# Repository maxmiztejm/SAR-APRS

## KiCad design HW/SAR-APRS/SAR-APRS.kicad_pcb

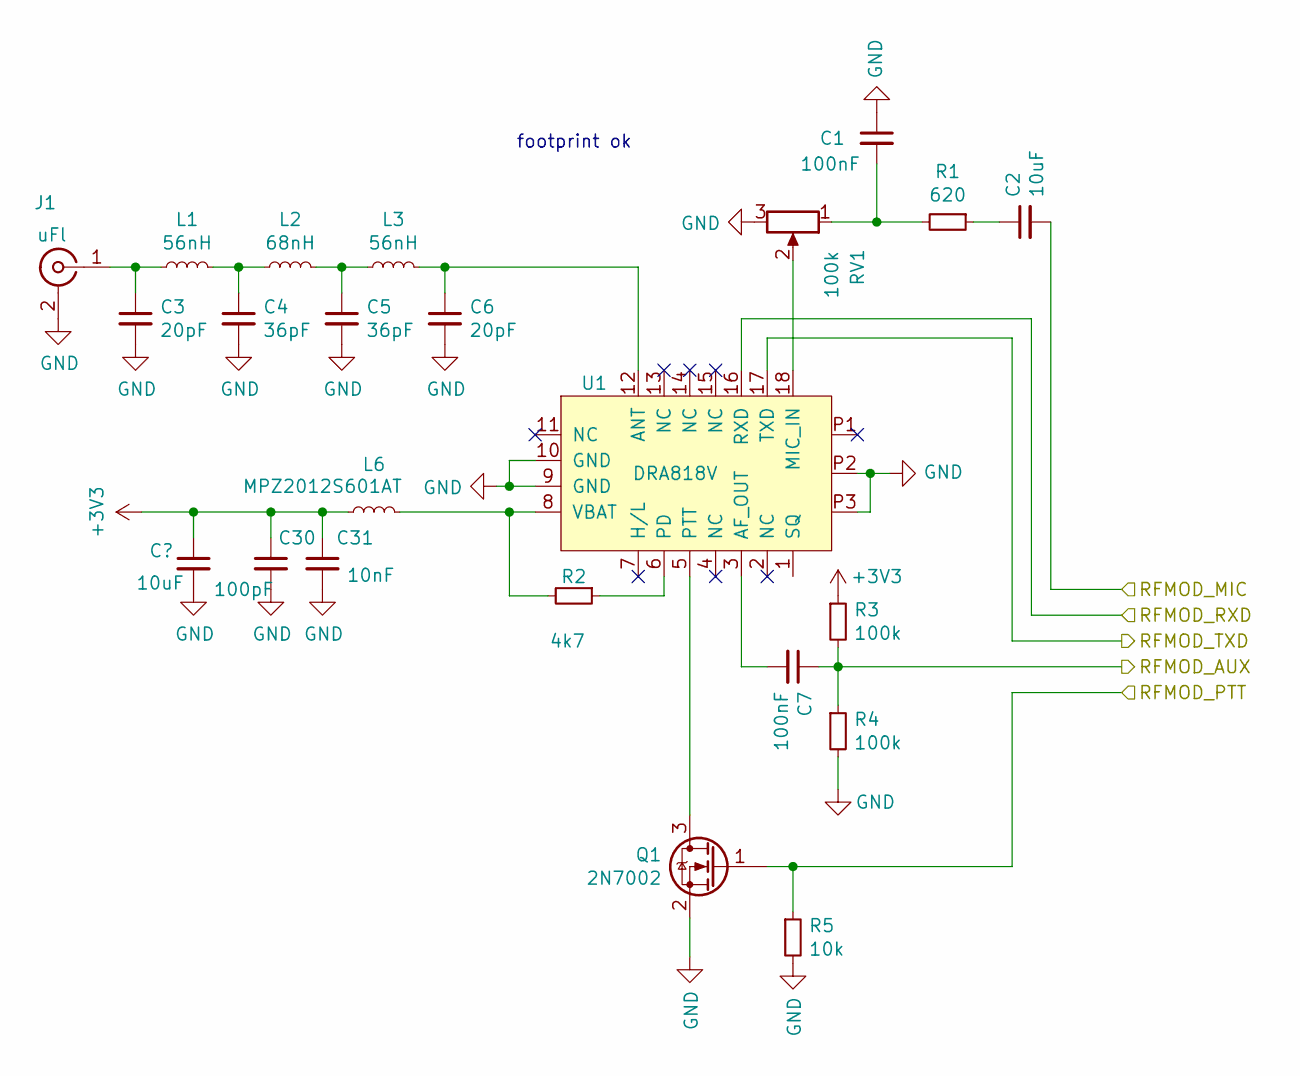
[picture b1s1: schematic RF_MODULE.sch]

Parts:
C1, C7: 100nF; C_0805
C2: 10uF; C_0805
C3, C6: 20pF; C_0805
C4, C5: 36pF; C_0805
C30: 100pF; C_0603
C31: 10nF; C_0603
J1: uFl; sma_straight_32k101-400l5
L1, L3: 56nH; L_0805
L2: 68nH; L_0805
L6: MPZ2012S601AT; C_0805
Q1: 2N7002; SOT-23
R1: 620; R_0805
R2: 4k7; R_0805
R3, R4: 100k; R_0805
R5: 10k; R_0805
RV1: 100k; Potentiometer_Trimmer_Bourns_3214J
U1: DRA818V; DRA818

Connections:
/CPU/RFMOD_AUX: C7.1, R3.2, R4.1; also elsewhere on the board
/CPU/RFMOD_MIC: C2.2; also elsewhere on the board
/CPU/RFMOD_PTT: Q1.1 (G), R5.1; also elsewhere on the board
/CPU/RFMOD_RXD: U1.16 (RXD); also elsewhere on the board
/CPU/RFMOD_TXD: U1.17 (TXD); also elsewhere on the board
GND: C1.1, C3.2, C4.2, C5.2, C6.2, C30.2, C31.2, J1.2 (Ext), Q1.2 (S), R4.2, R5.2, RV1.3, U1.9 (GND), U1.10 (GND), U1.P2, U1.P3; also elsewhere on the board
unnamed: C1.2, R1.2, RV1.1
unnamed: C2.1, R1.1
unnamed: C3.1, J1.1 (In), L1.1
unnamed: C4.1, L1.2, L2.1
unnamed: C5.1, L2.2, L3.1
unnamed: C6.1, L3.2, U1.12 (ANT)
unnamed: C7.2, U1.3 (AF_OUT)
unnamed: L6.2, R2.2, U1.8 (VBAT)
unnamed: Q1.3 (D), U1.5 (PTT)
unnamed: R2.1, U1.6 (PD)
unnamed: RV1.2, U1.18 (MIC_IN)

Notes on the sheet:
footprint ok

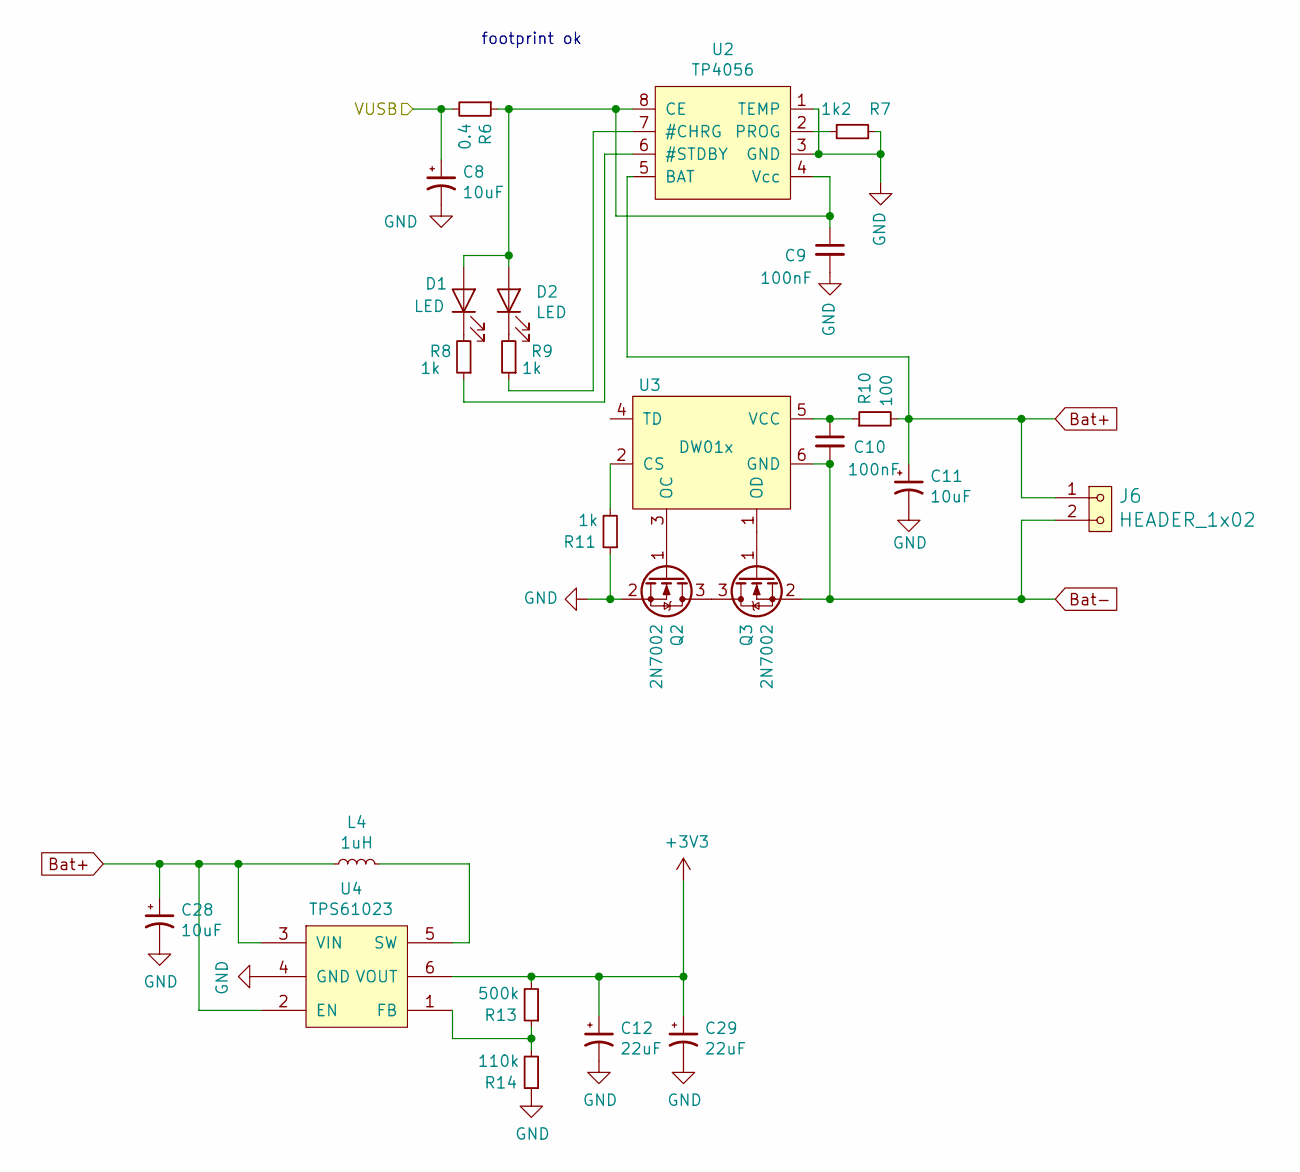
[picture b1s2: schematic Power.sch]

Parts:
C8, C11, C28: 10uF; C_1210
C9, C10: 100nF; C_0805
C12, C29: 22uF; C_1210
D1, D2: LED; LED_0805
J6: HEADER_1x02; Straight_1x02
L4: 1uH; L_6.3x6.3_H3
Q2, Q3: 2N7002; SOT-23
R6: 0.4; R_2512
R7: 1k2; R_0805
R8, R9, R11: 1k; R_0805
R10: 100; R_0805
R13: 500k; R_0805
R14: 110k; R_0805
U2: TP4056; SO-8_3.9x4.9mm_P1.27mm
U3: DW01x; SOT-23-6
U4: TPS61023; SOT-563

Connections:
/CPU/VUSB: C8.1, R6.2; also elsewhere on the board
Bat+: C11.1, C28.1, J6.1, L4.1, R10.2, U2.5 (BAT), U4.2 (EN), U4.3 (VIN); also elsewhere on the board
Bat-: C10.2, J6.2, Q3.2 (S), U3.6 (GND)
GND: C8.2, C9.2, C11.2, C12.2, C28.2, C29.2, Q2.2 (S), R7.2, R11.1, R14.1, U2.1 (TEMP), U2.3 (GND), U4.4 (GND); also elsewhere on the board
unnamed: C9.1, D1.2 (A), D2.2 (A), R6.1, U2.4 (Vcc), U2.8 (CE)
unnamed: C10.1, R10.1, U3.5 (VCC)
unnamed: D1.1 (K), R8.2
unnamed: D2.1 (K), R9.2
unnamed: L4.2, U4.5 (SW)
unnamed: Q2.1 (G), U3.3 (OC)
unnamed: Q2.3 (D), Q3.3 (D)
unnamed: Q3.1 (G), U3.1 (OD)
unnamed: R7.1, U2.2 (PROG)
unnamed: R8.1, U2.6 (#STDBY)
unnamed: R9.1, U2.7 (#CHRG)
unnamed: R11.2, U3.2 (CS)
unnamed: R13.1, R14.2, U4.1 (FB)

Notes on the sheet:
footprint ok

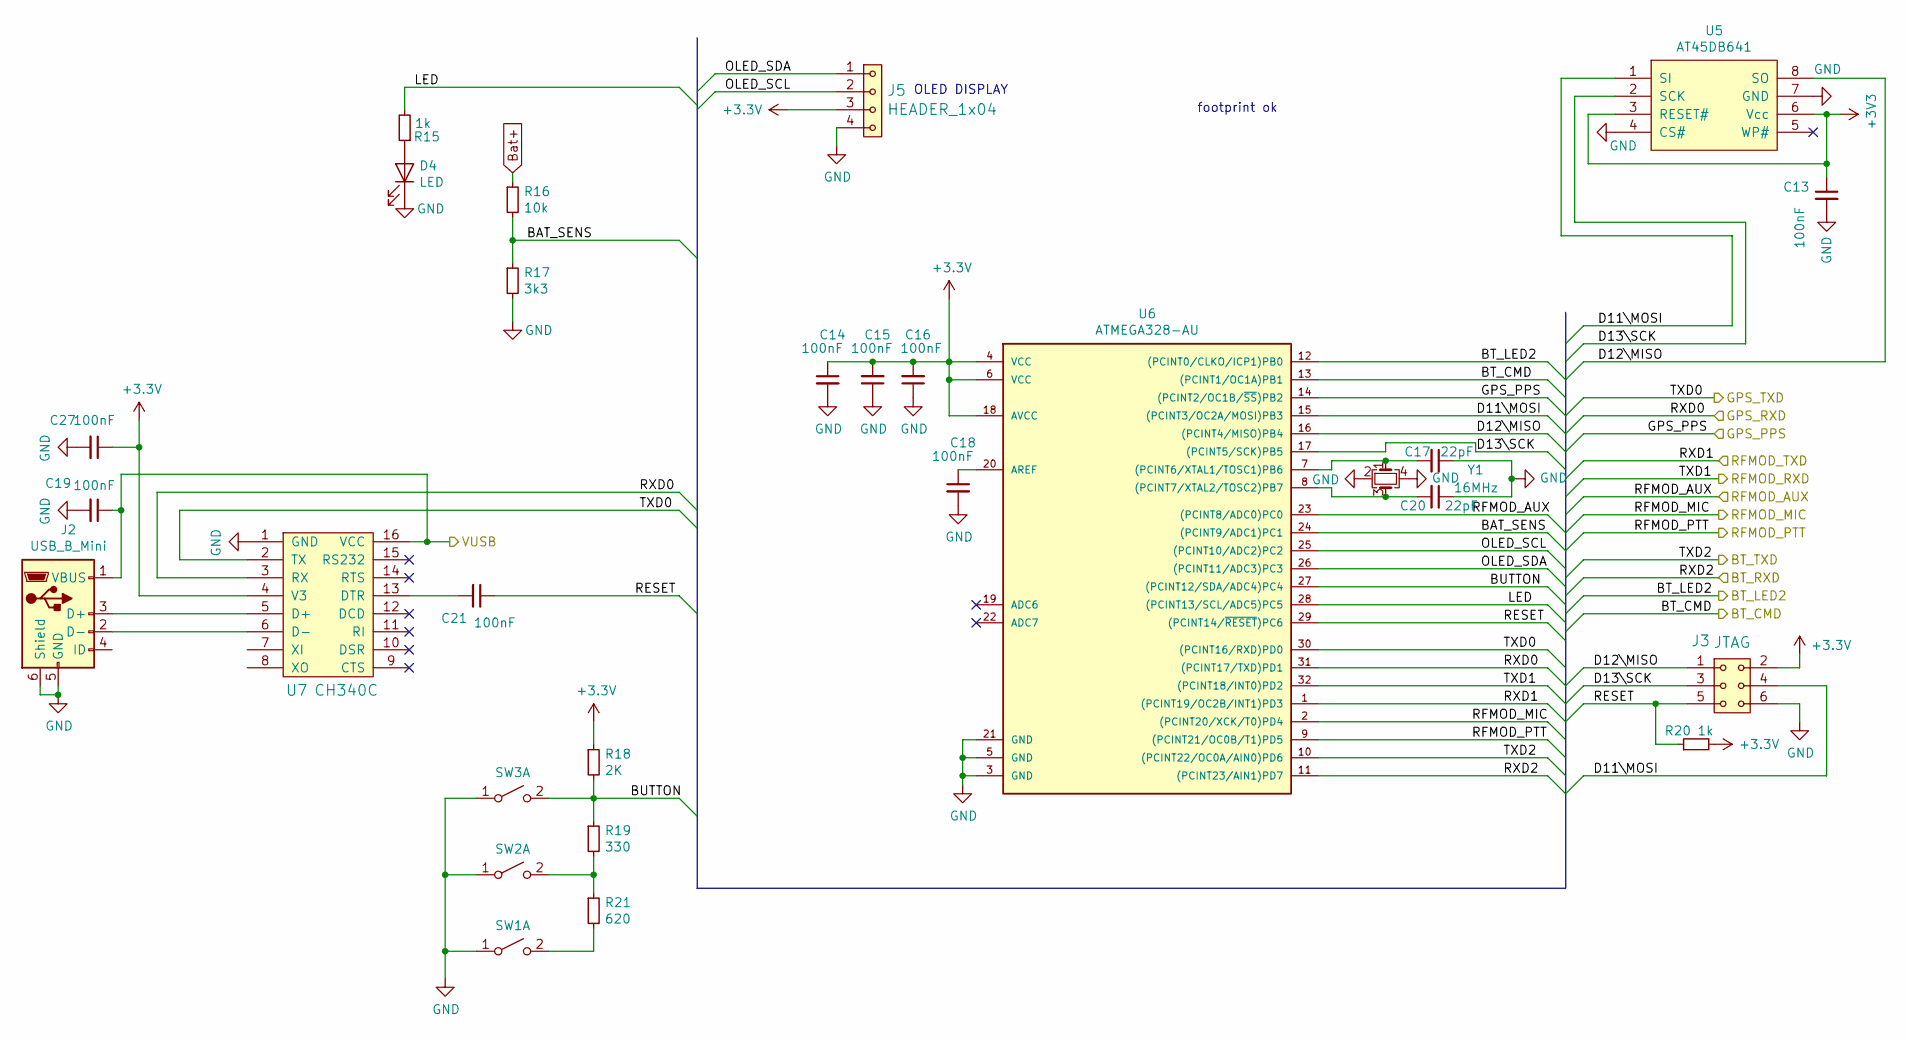
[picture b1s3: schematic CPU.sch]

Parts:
C13, C14, C15, C16, C18, C19, C21, C27: 100nF; C_0805
C17, C20: 22pF; C_0805
D4: LED; LED_0805
J2: USB_B_Mini; USB_Mini-B
J3: JTAG; Straight_2x03
J5: HEADER_1x04; Straight_1x04
R15, R20: 1k; R_0805
R16: 10k; R_0805
R17: 3k3; R_0805
R18: 2K; R_0805
R19: 330; R_0805
R21: 620; R_0805
SW1, SW2, SW3: SW_DPST_x2; SW_SPST_EVQP0
U5: AT45DB641; SOIC-8_3.9x4.9mm_Pitch1.27mm
U6: ATMEGA328-AU; TQFP-32_7x7mm_Pitch0.8mm
U7: CH340C; SOP-16_4.55x10.3mm_P1.27mm
Y1: 16MHz; ISM81

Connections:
/BT_module/BT_CMD: U6.13 ((PCINT1/OC1A)PB1); also elsewhere on the board
/BT_module/BT_LED2: U6.12 ((PCINT0/CLKO/ICP1)PB0); also elsewhere on the board
/BT_module/BT_RXD: U6.11 ((PCINT23/AIN1)PD7); also elsewhere on the board
/BT_module/BT_TXD: U6.10 ((PCINT22/OC0A/AIN0)PD6); also elsewhere on the board
/CPU/BAT_SENS: R16.2, R17.1, U6.24 ((PCINT9/ADC1)PC1)
/CPU/BUTTON: R18.2, R19.1, SW3.2 (B), U6.27 ((PCINT12/SDA/ADC4)PC4)
/CPU/D11\MOSI: J3.4, U5.1 (SI), U6.15 ((PCINT3/OC2A/MOSI)PB3)
/CPU/D12\MISO: J3.1, U5.8 (SO), U6.16 ((PCINT4/MISO)PB4)
/CPU/D13\SCK: J3.3, U5.2 (SCK), U6.17 ((PCINT5/SCK)PB5)
/CPU/GPS_PPS: U6.14 ((PCINT2/OC1B/~SS~)PB2); also elsewhere on the board
/CPU/GPS_RXD: U6.31 ((PCINT17/TXD)PD1), U7.3 (RX); also elsewhere on the board
/CPU/LED: R15.2, U6.28 ((PCINT13/SCL/ADC5)PC5)
/CPU/OLED_SCL: J5.2, U6.25 ((PCINT10/ADC2)PC2)
/CPU/OLED_SDA: J5.1, U6.26 ((PCINT11/ADC3)PC3)
/CPU/RESET: C21.1, J3.5, R20.1, U6.29 ((PCINT14/~RESET~)PC6)
/CPU/RFMOD_AUX: U6.23 ((PCINT8/ADC0)PC0); also elsewhere on the board
/CPU/RFMOD_MIC: U6.2 ((PCINT20/XCK/T0)PD4); also elsewhere on the board
/CPU/RFMOD_PTT: U6.9 ((PCINT21/OC0B/T1)PD5); also elsewhere on the board
/CPU/RFMOD_RXD: U6.32 ((PCINT18/INT0)PD2); also elsewhere on the board
/CPU/RFMOD_TXD: U6.1 ((PCINT19/OC2B/INT1)PD3); also elsewhere on the board
/CPU/VUSB: C19.1, J2.1 (VBUS), U7.16 (VCC); also elsewhere on the board
/GPS/GPS_RXD: U6.30 ((PCINT16/RXD)PD0), U7.2 (TX); also elsewhere on the board
Bat+: R16.1; also elsewhere on the board
GND: C13.2, C14.2, C15.1, C16.1, C17.1, C18.2, C19.2, C20.1, C27.2, D4.1 (K), J2.5 (GND), J2.6 (Shield), J3.6, J5.4, R17.2, SW1.1 (A), SW2.1 (A), SW3.1 (A), U5.4 (CS#), U5.7 (GND), U6.3 (GND), U6.5 (GND), U6.21 (GND), U7.1 (GND), Y1.2, Y1.4; also elsewhere on the board
unnamed: C17.2, U6.7 ((PCINT6/XTAL1/TOSC1)PB6), Y1.1
unnamed: C18.1, U6.20 (AREF)
unnamed: C20.2, U6.8 ((PCINT7/XTAL2/TOSC2)PB7), Y1.3
unnamed: C21.2, U7.13 (DTR)
unnamed: D4.2 (A), R15.1
unnamed: J2.2 (D-), U7.6 (D-)
unnamed: J2.3 (D+), U7.5 (D+)
unnamed: R19.2, R21.1, SW2.2 (B)
unnamed: R21.2, SW1.2 (B)

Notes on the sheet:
OLED DISPLAY
footprint ok

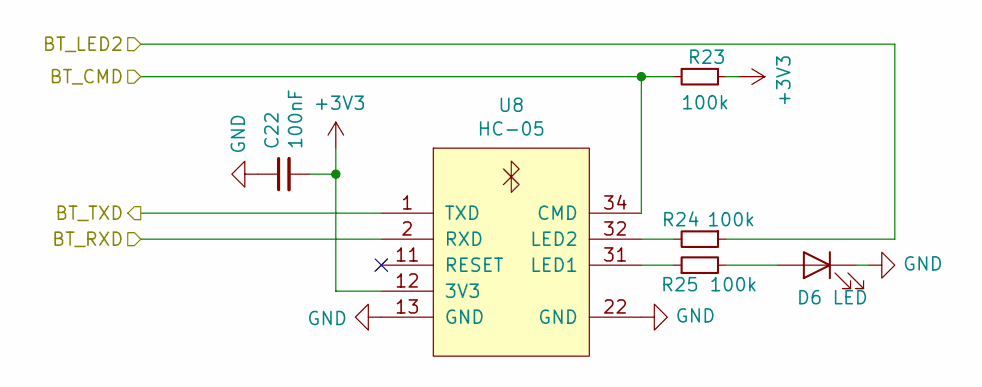
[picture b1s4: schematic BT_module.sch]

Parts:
C22: 100nF; C_0805
D6: LED; LED_0805
R23, R24, R25: 100k; R_0805
U8: HC-05; HC-05 BT

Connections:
/BT_module/BT_CMD: R23.2, U8.34 (CMD); also elsewhere on the board
/BT_module/BT_LED2: R24.1; also elsewhere on the board
/BT_module/BT_RXD: U8.2 (RXD); also elsewhere on the board
/BT_module/BT_TXD: U8.1 (TXD); also elsewhere on the board
GND: C22.1, D6.1 (K), U8.13 (GND), U8.22 (GND); also elsewhere on the board
unnamed: D6.2 (A), R25.2
unnamed: R24.2, U8.32 (LED2)
unnamed: R25.1, U8.31 (LED1)

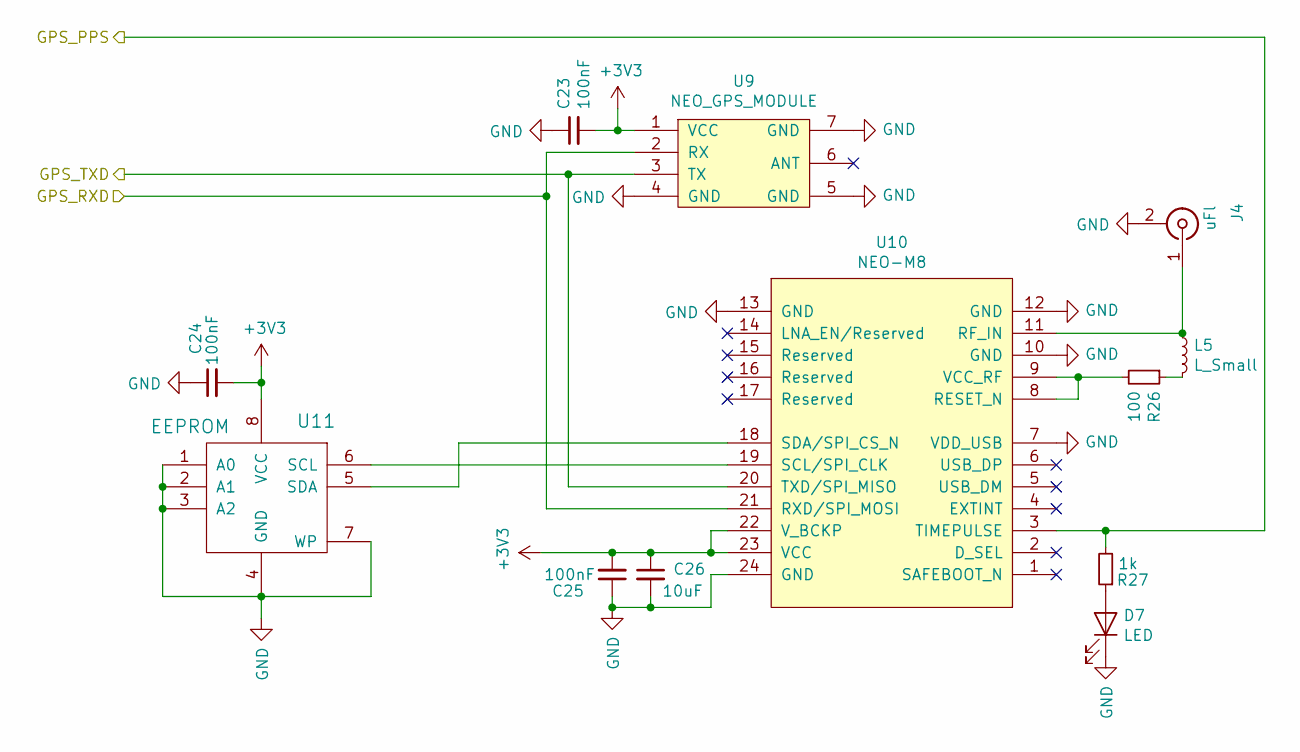
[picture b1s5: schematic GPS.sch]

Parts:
C23, C24, C25: 100nF; C_0805
C26: 10uF; C_1210
D7: LED; LED_0805
J4: uFl; coaxial_u.fl-r-smt-1
L5: L_Small; L_0805
R26: 100; R_0805
R27: 1k; R_0805
U9: NEO_GPS_MODULE; Straight_1x04
U10: NEO-M8; ublox_NEO
U11: EEPROM; TSSOP-8_4.4x3mm_P0.65mm

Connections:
/CPU/GPS_PPS: R27.2, U10.3 (TIMEPULSE); also elsewhere on the board
/CPU/GPS_RXD: U9.3 (TX), U10.20 (TXD/SPI_MISO); also elsewhere on the board
/GPS/GPS_RXD: U9.2 (RX), U10.21 (RXD/SPI_MOSI); also elsewhere on the board
GND: C23.1, C24.1, C25.1, C26.2, D7.1 (K), J4.2 (Ext), U9.4 (GND), U9.5 (GND), U9.7 (GND), U10.7 (VDD_USB), U10.10 (GND), U10.12 (GND), U10.13 (GND), U10.24 (GND), U11.1 (A0), U11.2 (A1), U11.3 (A2), U11.4 (GND), U11.7 (WP); also elsewhere on the board
unnamed: D7.2 (A), R27.1
unnamed: J4.1 (In), L5.1, U10.11 (RF_IN)
unnamed: L5.2, R26.1
unnamed: R26.2, U10.8 (RESET_N), U10.9 (VCC_RF)
unnamed: U10.18 (SDA/SPI_CS_N), U11.5 (SDA)
unnamed: U10.19 (SCL/SPI_CLK), U11.6 (SCL)

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
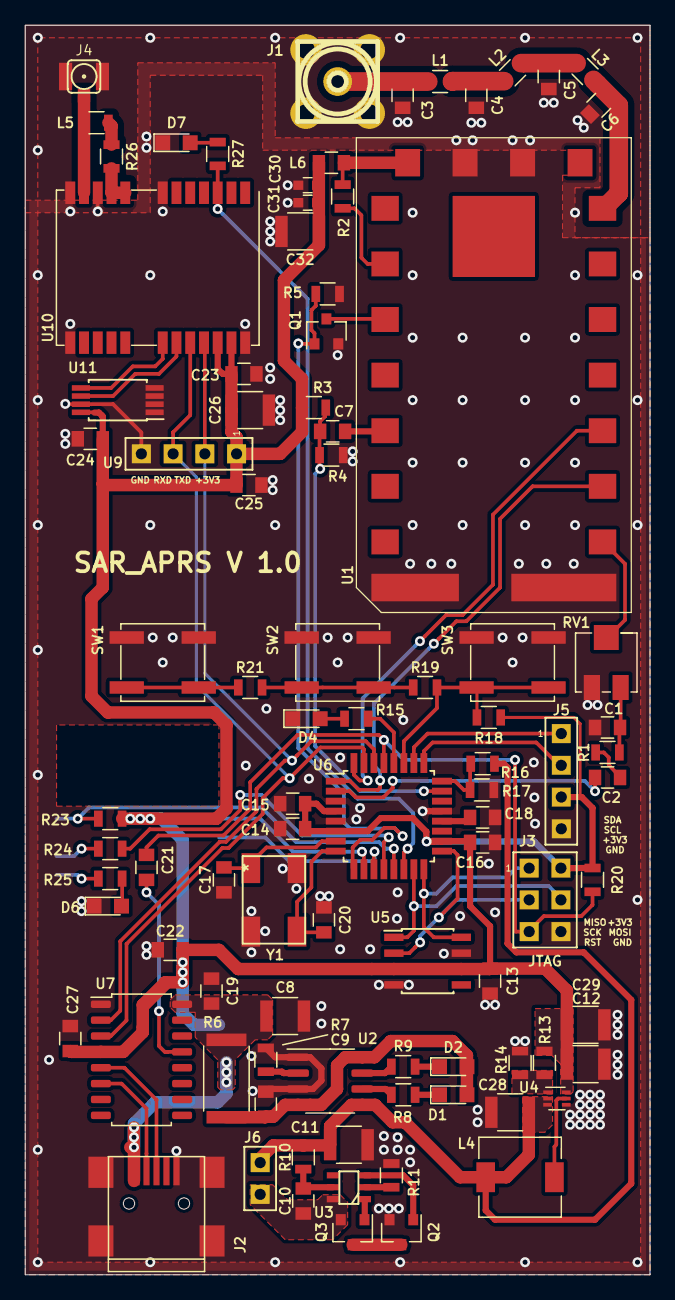
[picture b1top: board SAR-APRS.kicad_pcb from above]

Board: 2 copper layers, 50.0 x 100.0 mm, 93 parts (1 on the bottom side), 68 nets.

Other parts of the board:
C32: 10uF; C_1210

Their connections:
GND: C32.2; also elsewhere on the board

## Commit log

2018-10-06 FW
    copy from project trackuino1.51_rev2
2018-11-23 schematic update
2018-12-15 schematic update memmory adding
2019-03-29 schem and pcb update
2019-03-31 schm and pcb update
2019-04-23 PCB update
2020-02-24 adding gerbers and bom
2020-03-08 DC-DC changed, PCB update
2020-03-15 ibom added
2020-05-20 gerbers update
